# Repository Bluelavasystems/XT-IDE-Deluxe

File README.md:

Blue lava systems XT-IDE Deluxe ReadMe
----

Bootable 8-bit ISA CF+IDE interface

Documentation for the switches can be found on the rear silkscreen.

Credit:
----
Design by monotech pcs

Design uses some of the schematic from XT-IDE Rev2 and Glitchworks
www.vcfed.org/forum/showthread.php?29202-XTIDE-Rev2
github.com/glitchwrks/xt_ide

XT-IDE Universal BIOS
www.xtideuniversalbios.org

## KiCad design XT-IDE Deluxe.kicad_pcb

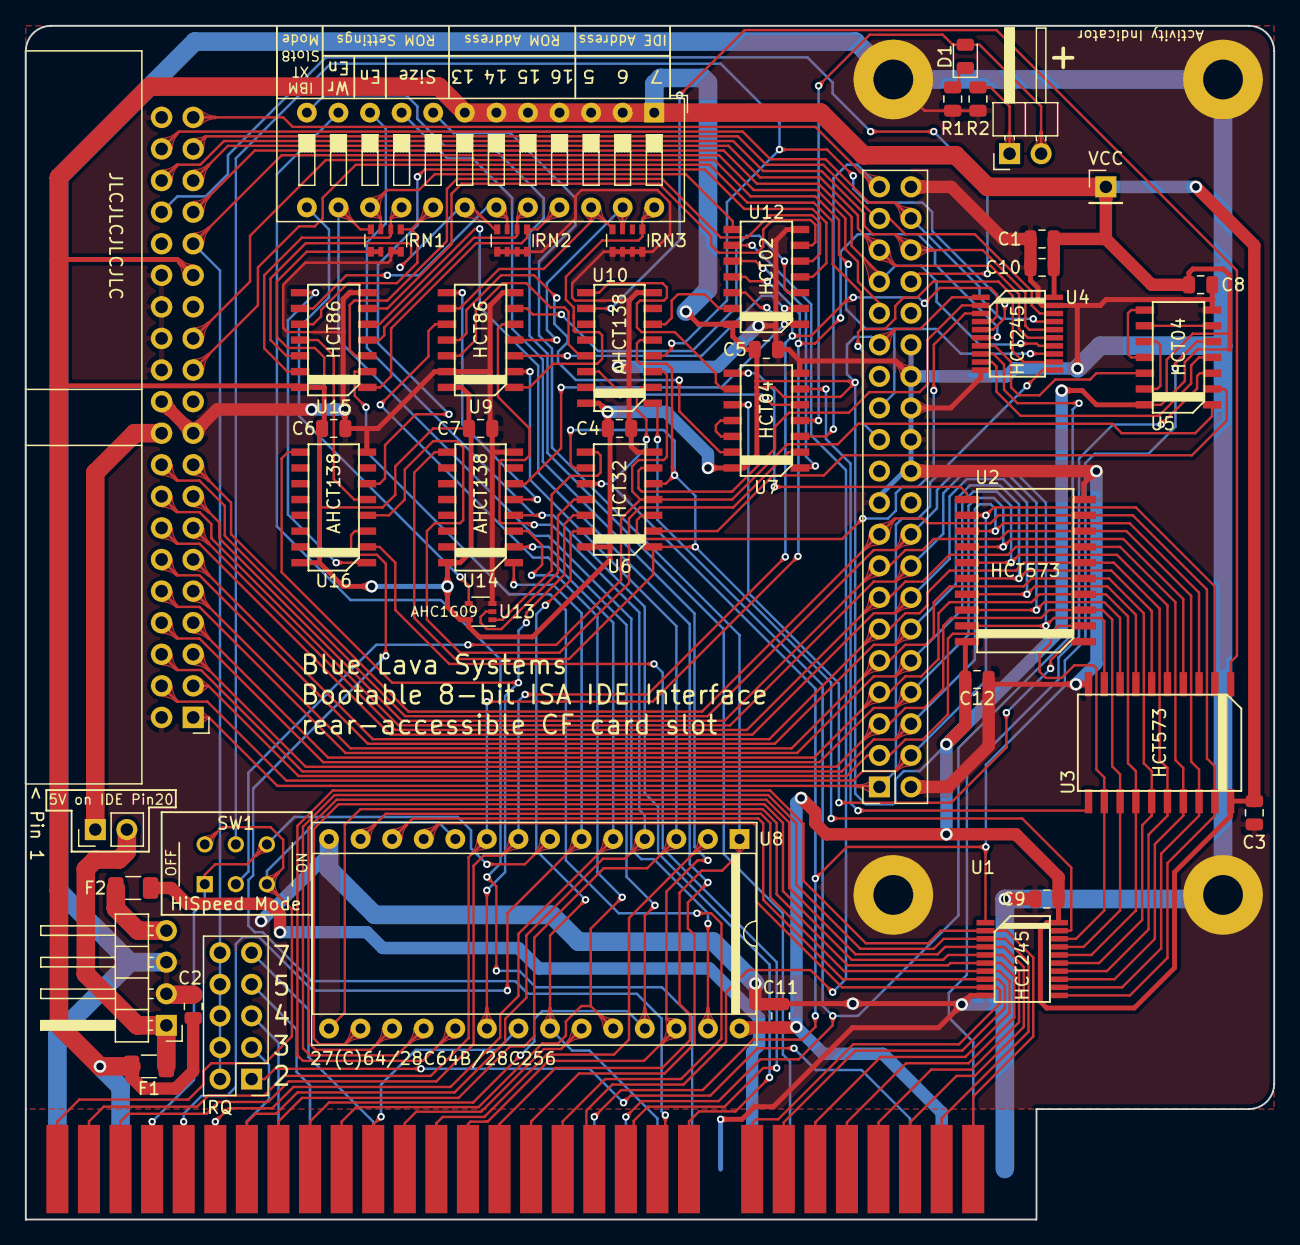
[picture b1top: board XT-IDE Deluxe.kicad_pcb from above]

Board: 2 copper layers, 100.4 x 96.0 mm, 49 parts (0 on the bottom side), 123 nets.

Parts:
BUS1: Bus_ISA_8bit; ISA-8BIT-XT-IDE
C1, C2: 106; C_0805_2012Metric
C3, C4, C5, C6, C7, C8, C9, C10, C11, C12: 104; C_0805_2012Metric
D1: LED; LED_0805_2012Metric
D2: LED; PinHeader_1x02_P2.54mm_Horizontal
F1, F2: 1.5A; Fuse_1206_3216Metric
H1, H2, H3, H4: M3; MountingHole_3.2mm_M3_Pad
J1: IDE; IDC-Header_2x20_P2.54mm_Horizontal
J2: CF_Adapter; PinSocket_2x20_P2.54mm_Vertical
J3: IRQ; PinHeader_2x05_P2.54mm_Vertical
J4: VCC; PinHeader_1x01_P2.54mm_Vertical
J5: Power Output; PinHeader_1x04_P2.54mm_Horizontal
JP1: 5V on IDE Pin20; PinHeader_1x02_P2.54mm_Vertical
R1, R2: 1k; R_0805_2012Metric
RN1, RN2, RN3: 10k; R_Array_Convex_4x0603
SW1: HiSpeed; SW_MS-22D18G2
SW2: Config; SW_DIP_SPSTx12_Slide_9.78x32.66mm_W7.62mm_P2.54mm
U1, U4: HCT245; TSSOP-20_4.4x6.5mm_P0.65mm
U2, U3: HCT573; SOIC-20W_7.5x12.8mm_P1.27mm
U5, U7: HCT04; SOIC-14_3.9x8.7mm_P1.27mm
U6: HCT32; SOIC-14_3.9x8.7mm_P1.27mm
U8: 28C256; DIP-28_W15.24mm_Socket
U9, U15: HCT86; SOIC-14_3.9x8.7mm_P1.27mm
U10, U14, U16: AHCT138; SOIC-16_3.9x9.9mm_P1.27mm
U12: HCT02; SOIC-14_3.9x8.7mm_P1.27mm
U13: AHC1G09; SOT-353_SC-70-5

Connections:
+12V: BUS1.9, F2.1
/5V_Fused: F1.2, J5.1, JP1.2
/A0: BUS1.62, SW1.3, SW1.4, U8.10
/A0-OR-3: SW1.5, U4.5, U10.4
/A1: BUS1.61, U4.6, U8.9, U12.11
/A2: BUS1.60, U4.4, U8.8, U12.12
/A3: BUS1.59, SW1.1, SW1.6, U8.7
/A3-OR-0: SW1.2, U5.1, U6.4, U10.3
/A4: BUS1.58, U8.6, U14.1
/A5: BUS1.57, U8.5, U9.10
/A6: BUS1.56, U8.4, U9.5
/A7: BUS1.55, U8.3, U9.2
/A8: BUS1.54, U8.25, U14.2
/A9: BUS1.53, U8.24, U14.3
/A10: BUS1.52, U8.21
/A11: BUS1.51, U8.23
/A12: BUS1.50, U8.2
/A13: BUS1.49, SW2.9, U8.26
/A14: BUS1.48, SW2.8, U8.1
/A15: BUS1.47, U15.5
/A16: BUS1.46, U15.2
/A17: BUS1.45, U12.9
/A18: BUS1.44, U16.2
/A19: BUS1.43, U16.3
/AEN: BUS1.42, SW2.10, U14.4
/BA0-OR-BA3: J1.35, J2.35, U4.15
/BA1: J1.33, J2.33, U4.14
/BA2: J1.36, J2.36, U4.16
/D0: BUS1.40, U1.9, U8.11
/D1: BUS1.39, U1.8, U8.12
/D2: BUS1.38, U1.7, U8.13
/D3: BUS1.37, U1.6, U8.15
/D4: BUS1.36, U1.5, U8.16
/D5: BUS1.35, U1.4, U8.17
/D6: BUS1.34, U1.3, U8.18
/D7: BUS1.33, U1.2, U8.19
/DB0: J1.17, J2.17, U1.11, U2.9, U3.19
/DB1: J1.15, J2.15, U1.12, U2.8, U3.18
/DB2: J1.13, J2.13, U1.13, U2.7, U3.17
/DB3: J1.11, J2.11, U1.14, U2.6, U3.16
/DB4: J1.9, J2.9, U1.15, U2.5, U3.15
/DB5: J1.7, J2.7, U1.16, U2.4, U3.14
/DB6: J1.5, J2.5, U1.17, U2.3, U3.13
/DB7: J1.3, J2.3, U1.18, U2.2, U3.12
/DB8: J1.4, J2.4, U2.12, U3.2
/DB9: J1.6, J2.6, U2.13, U3.3
/DB10: J1.8, J2.8, U2.14, U3.4
/DB11: J1.10, J2.10, U2.15, U3.5
/DB12: J1.12, J2.12, U2.16, U3.6
/DB13: J1.14, J2.14, U2.17, U3.7
/DB14: J1.16, J2.16, U2.18, U3.8
/DB15: J1.18, J2.18, U2.19, U3.9
/IDE_5V: J1.20, JP1.1
/IDE_A5: RN3.4, SW2.22, U9.9
/IDE_A6: RN3.3, SW2.23, U9.4
/IDE_A7: RN3.1, SW2.24, U9.1
/IDE_IRQ: J1.31, J2.31, J3.2, J3.4, J3.6, J3.8, J3.10
/IRQ2: BUS1.4, J3.1
/IRQ3: BUS1.25, J3.3
/IRQ4: BUS1.24, J3.5
/IRQ5: BUS1.23, J3.7
/IRQ7: BUS1.21, J3.9
/ROM_8K_1: RN1.1, SW2.17, U15.10
/ROM_8K_2: RN1.2, SW2.16, U15.13
/ROM_A13: RN2.4, SW2.18, U15.12
/ROM_A14: RN2.3, SW2.19, U15.9
/ROM_A15: RN2.2, SW2.20, U15.4
/ROM_A16: RN2.1, SW2.21, U15.1
/RST: BUS1.2, U5.3
/~BIOR: J1.25, J2.25, U4.13
/~BIOW: J1.23, J2.23, U4.12
/~BRST: J1.1, J2.1, U4.11
/~CS1: J1.37, J2.37, U4.18
/~CS3: J1.38, J2.38, U4.17
/~DASP: J1.39, J2.39, U7.3
/~IDE_CS: U1.19, U6.1, U6.5, U6.9, U10.5, U14.9
/~IOR: BUS1.14, U1.1, U5.5, U6.10, U10.2
/~IOR_DELAY: U4.7, U5.12
/~IOW: BUS1.13, U4.8, U10.1
/~LA1-OE: U3.1, U10.10
/~LA1_Strobe: U3.11, U7.6
/~LA2-OE: U2.1, U7.10
/~LA2_Strobe: U2.11, U7.8
/~MEMR: BUS1.12, U6.13, U8.22
/~MEMW: BUS1.11, SW2.11
/~PDIAG: J1.34, J2.34
/~ROM_CS: U6.12, U8.20, U16.9
/~ROM_EN: RN1.3, SW2.15, U12.8
/~ROM_WR: RN1.4, SW2.14, U8.27
/~RST: U4.9, U5.4
/~Slot8: BUS1.8, SW2.12
/~xCS1: U4.2, U6.6
/~xCS3: U4.3, U6.3
/~xLA2-OE: U9.12, U10.13
/~xSlot8: SW2.13, U13.4
GND: BUS1.1, BUS1.10, BUS1.31, C1.2, C2.2, C3.2, C4.2, C5.2, C6.2, C7.2, C8.2, C9.2, C10.2, C11.2, C12.2, H1.1, H2.1, H3.1, H4.1, J1.2, J1.19, J1.22, J1.24, J1.26, J1.28, J1.30, J1.40, J2.2, J2.19, J2.22, J2.24, J2.26, J2.28, J2.30, J2.40, J5.2, J5.3, R1.1, R2.1, RN1.7, RN1.8, RN2.5, RN2.6, RN2.7, RN2.8, RN3.5, RN3.6, RN3.7, RN3.8, U1.10, U2.10, U3.10, U4.10, U4.19, U5.7, U6.7, U7.7, U8.14, U9.7, U9.13, U10.8, U12.7, U13.3, U14.8, U15.7, U16.8
unnamed: D1.1, R1.2
unnamed: D1.2, D2.2, U7.4
unnamed: D2.1, R2.2
unnamed: F2.2, J5.4
unnamed: U5.2, U6.2
unnamed: U5.6, U5.9
unnamed: U5.10, U5.13
unnamed: U5.8, U5.11
unnamed: U7.11, U7.12
unnamed: U7.13, U9.11
unnamed: U10.6, U12.13
unnamed: U7.9, U10.9
unnamed: U7.5, U10.14
unnamed: U12.1, U14.6
unnamed: U9.3, U12.2
unnamed: U9.6, U12.3
unnamed: U12.4, U16.6
unnamed: U12.5, U15.3
unnamed: U12.6, U15.6
unnamed: U7.1, U12.10
unnamed: U6.8, U13.1
unnamed: U6.11, U13.2
unnamed: U9.8, U14.5
unnamed: U15.8, U16.1
unnamed: U15.11, U16.5
unnamed: U7.2, U16.4
VCC: BUS1.3, BUS1.29, C1.1, C2.1, C3.1, C4.1, C5.1, C6.1, C7.1, C8.1, C9.1, C10.1, C11.1, C12.1, F1.1, J1.29, J2.29, J4.1, RN1.5, RN1.6, SW2.1, SW2.2, SW2.3, SW2.4, SW2.5, SW2.6, SW2.7, U1.20, U2.20, U3.20, U4.1, U4.20, U5.14, U6.14, U7.14, U8.28, U9.14, U10.16, U12.14, U13.5, U14.16, U15.14, U16.16
